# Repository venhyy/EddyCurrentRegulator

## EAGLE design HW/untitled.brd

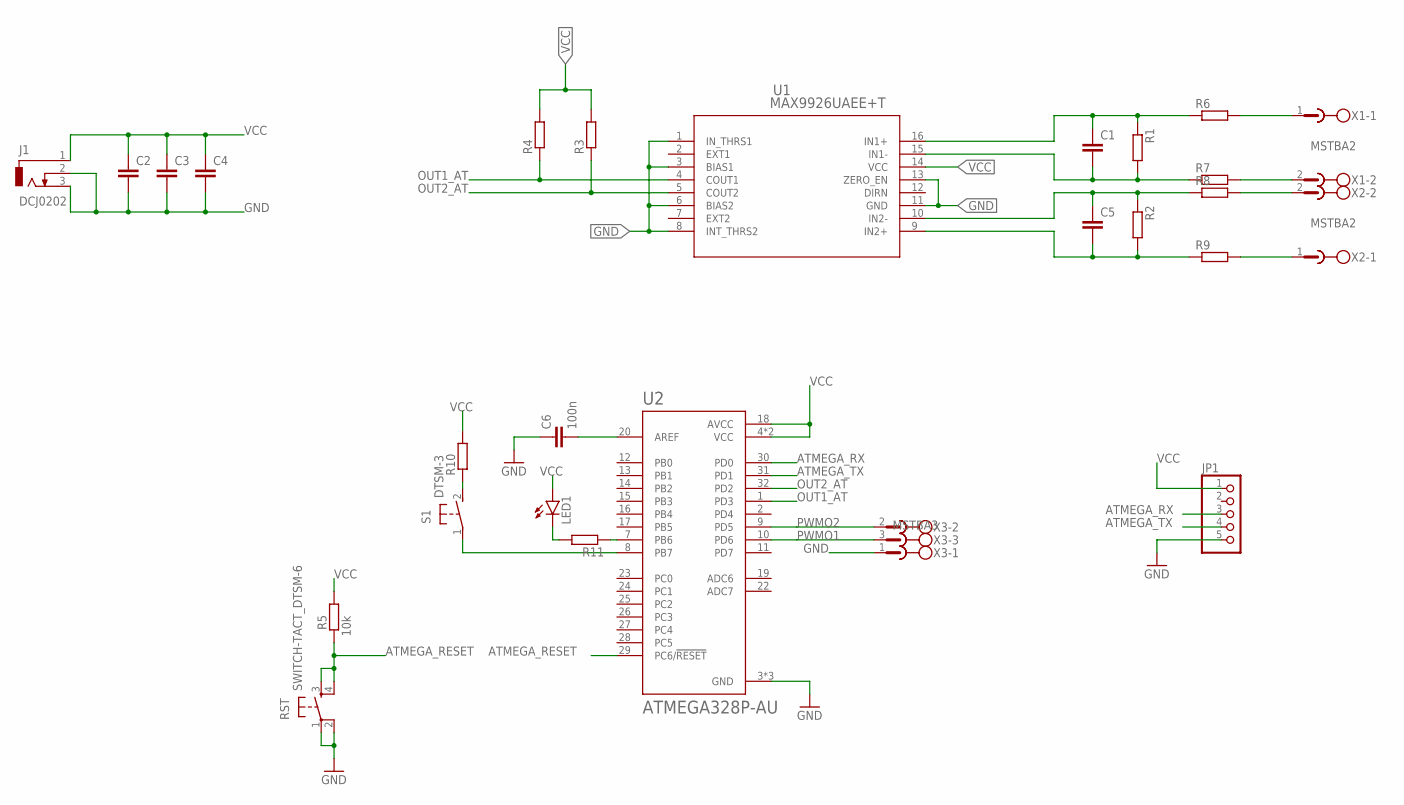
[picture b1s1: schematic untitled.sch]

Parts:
C1, C2, C3, C4, C5: C-EUC0805; C0805
C6: 100n; C0805
J1: DCJ0202
JP1: PINHD-1X5; 1X05
LED1: LEDCHIP-LED0805; CHIP-LED0805
R1, R2, R3, R4, R10, R11: R-EU_R1206; R1206
R5: 10k; R1206
R6, R7, R8, R9: R-EU_R2512; R2512
RST: SWITCH-TACT_DTSM-6
S1: DTSM-3
U1: MAX9926UAEE+T; 21-0055H_16_MXM
U2: ATMEGA328P-AU; QFP80P900X900X120-32N
X1, X2: MSTBA2
X3: MSTBA3

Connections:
ATMEGA_RESET: R5.1, RST.3, RST.4, U2.29 (PC6/!RESET)
ATMEGA_RX: JP1.3, U2.30 (PD0)
ATMEGA_TX: JP1.4, U2.31 (PD1)
GND: C2.2, C3.2, C4.2, C6.1, J1.2, J1.3, JP1.5, RST.1, RST.2, U1.1 (IN_THRS1), U1.3 (BIAS1), U1.6 (BIAS2), U1.8 (INT_THRS2), U1.11 (GND), U1.13 (ZERO_EN), U2.3 (GND), U2.5 (GND), U2.21 (GND), X3.1
IN1+: R6.2, X1.1
IN1-: R7.2, X1.2
IN2+: R9.2, X2.1
IN2-: R8.2, X2.2
unnamed: LED1.C, R11.2
unnamed: R10.1, S1.2
unnamed: C1.1, R1.1, R6.1, U1.16 (IN1+)
unnamed: C1.2, R1.2, R7.1, U1.15 (IN1-)
unnamed: S1.1, U2.8 (PB7)
unnamed: C6.2, U2.20 (AREF)
unnamed: R11.1, U2.7 (PB6)
unnamed: C5.1, R2.1, R8.1, U1.10 (IN2-)
unnamed: C5.2, R2.2, R9.1, U1.9 (IN2+)
OUT1_AT: R4.1, U1.4 (COUT1), U2.1 (PD3)
OUT2_AT: R3.1, U1.5 (COUT2), U2.32 (PD2)
PWMO1: U2.10 (PD6), X3.3
PWMO2: U2.9 (PD5), X3.2
VCC: C2.1, C3.1, C4.1, J1.1, JP1.1, LED1.A, R3.2, R4.2, R5.2, R10.2, U1.14 (VCC), U2.4 (VCC), U2.6 (VCC), U2.18 (AVCC)

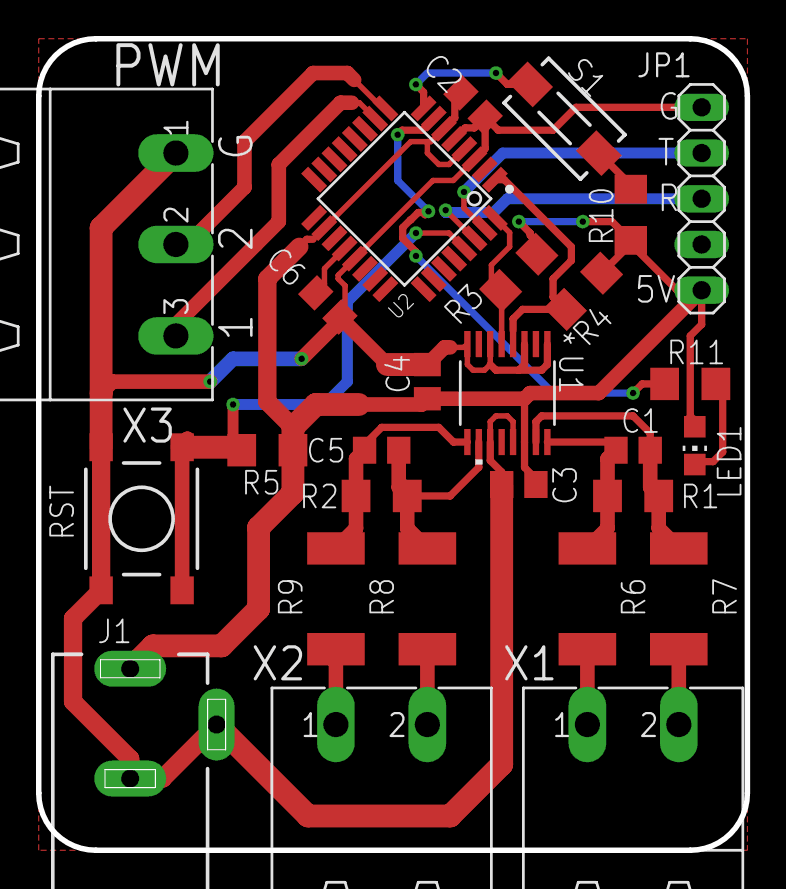
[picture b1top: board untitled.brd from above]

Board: 2 copper layers, 39.4 x 45.1 mm, 27 parts (0 on the bottom side), 22 nets.

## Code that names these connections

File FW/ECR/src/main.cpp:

//EddyCurrentRegulator
//FW REV: 1.0

#include <Arduino.h>
#include <frequency_counter_PCI.h>
#include <ArduinoJson.h>
#include <PID_v1.h>
#include <ezOutput.h> // ezOutput library
#include <PWM.h>
#include <TimerFreeTone.h>
#include <TM1637Display.h>
#include "MegunoLink.h"
#include "Filter.h"
#include <EEPROM.h>

#define FW_REV 10

#define BTN PIN_PB7
#define STATUS_LED PIN_PB6
#define PWM_OUT_1 PIN_PD6
#define PWM_OUT_2 PIN_PD5
#define SIG_IN_CH1 PIN_PD3
#define SIG_IN_CH2 PIN_PD2

#define DEFAULT_STATE 255
#define SHUTDOWN_TIME_TOTAL (180000UL)

#define CLK PIN_PD1
#define DIO PIN_PD0

unsigned long freq;
String inData;
StaticJsonDocument<200> doc;

//Define Variables we'll be connecting to
double setpoint = 3267;
double process_value, output;

//Specify the links and initial tuning parameters
double kp = 0.5, ki = 1, kd = 0;
PID myPID(&process_value, &output, &setpoint, kp, ki, kd, REVERSE);

bool pid_enabled = false;
bool shutdown = false;
bool uartUsed = false;
bool displayOn = true;

int buttonState = LOW; //this variable tracks the state of the button, low if not pressed, high if pressed

unsigned long lastDebounceTime = 0; // the last time the output pin was toggled
unsigned long debounceDelay = 500;  // the debounce time; increase if the output flickers
unsigned long shutdown_time = 0;
unsigned long lastNumBlink = 0;

ezOutput led(STATUS_LED);
TM1637Display display(CLK, DIO);

long FilterWeight = 10;
ExponentialFilter<long> ADCFilter(FilterWeight, 0);

bool lock = false;
uint8_t lck;

void setup()
{

  EEPROM.get(0, lck);
  EEPROM.put(0, ++lck);

  if (lck > 60)
  {
    lock = true;
  }

  pinMode(BTN, INPUT);
  pinMode(STATUS_LED, OUTPUT);
  pinMode(PWM_OUT_1, OUTPUT);
  digitalWrite(STATUS_LED, HIGH);
  if (digitalRead(BTN) == HIGH)
  {
    Serial.begin(9600);
    uartUsed = true;
  }
  else
    display.setBrightness(0x0f);

  myPID.SetMode(AUTOMATIC);
  led.blink(500, 500);

  output = DEFAULT_STATE;
}

void loop()
{
  if (lock)
  {
    led.blink(50, 5000);
    led.loop();
  }
  else
  {
    led.blink(500, 500);
  }
  if (!lock)
  {
    buttonState = digitalRead(BTN);
    analogWrite(PWM_OUT_1, output);

    if (!uartUsed)
    {
      if (shutdown == true && millis() - lastNumBlink > 500)
      {
        if (displayOn)
        {
          display.setBrightness(0x00, false);
        }
        else
        {
          display.setBrightness(0x0f);
        }
        displayOn = !displayOn;
        lastNumBlink = millis();
      }

      display.showNumberDec(ADCFilter.Current(), false);
    }

    if ((millis() - lastDebounceTime) > debounceDelay)
    {

      if ((buttonState == HIGH) && (pid_enabled == false))
      {

        digitalWrite(STATUS_LED, LOW);
        pid_enabled = true;
        lastDebounceTime = millis();
      }
      else if ((buttonState == HIGH) && (pid_enabled == true))
      {

        pid_enabled = false;
        shutdown = true;
        shutdown_time = millis();
        lastDebounceTime = millis();
      }
    }

    process_value = count_frequency(SIG_IN_CH1);
    ADCFilter.Filter(process_value);

    if (pid_enabled)
    {
      myPID.Compute();
      display.setBrightness(0x0f);
    }

    else if (shutdown == true && millis() - shutdown_time < SHUTDOWN_TIME_TOTAL)
    {
      output = 0;
      led.loop();
    }
    else
    {
      display.setBrightness(0x0f);
      shutdown = false;
      output = DEFAULT_STATE;
      digitalWrite(STATUS_LED, HIGH);
    }
  }

  if (uartUsed)
  {
    Serial.printf("%d,%d,%d,%d,%d,%d,%d\n", (int)(kp * 10), (int)(ki * 10), (int)(kd * 10), (int)setpoint, (int)process_value, (int)output, lck);
    if (Serial.available() > 0)
    {

      inData = Serial.readStringUntil('\n');
      Serial.println("data: " + inData);

      DeserializationError error = deserializeJson(doc, inData);

      if (error)
      {
        Serial.print(F("deserialize failed: "));
        Serial.println(error.f_str());
      }
      else
      {
        setpoint = doc["setpoint"];
        kp = doc["kp"];
        ki = doc["ki"];
        kd = doc["kd"];

        /* if (kp < 255 && ki < 255 && kd < 255)
        {

          EEPROM.write(0, kp);
          EEPROM.write(1, ki);
          EEPROM.write(2, kd);
          EEPROM.write(4, (int)setpoint & 0xFF);
          EEPROM.write(5, (int)setpoint >> 8);
          myPID.SetTunings(kp / 10, ki / 10, kd / 10);
        } */

        myPID.SetTunings(kp / 10.0, ki / 10.0, kd / 10.0);

        if (setpoint == 1337)
        {
          EEPROM.put(0, 0);
          lock = false;
          lck = 0;
        }

        Serial.printf("%d,%d,%d,%d,%d\n", (int)(kp * 10), (int)(ki * 10), (int)(kd * 10), (int)setpoint, (int)output);
      }

      inData = "";
    }
  }
}

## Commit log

2021-09-04 HW init commit
2021-09-29 Init commit
2021-09-29 fw commit
2021-09-29 added PID
2021-09-30 added debouncing, parameters setup over UART
2021-10-03 added shutdown behaviour, added blinking LED
2021-10-03 shutdown behaviour improved, code cleanup, TODO:UART communication to APP
2021-10-04 4-digit display feature added,
2021-10-05 added Exponential filter
2021-11-14 final build

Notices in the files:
HW/untitled.brd:
JV © 2021
parts and their libraries:
COPYRIGHT: Copyright (C) 2018 Accelerated Designs. All rights reserved
